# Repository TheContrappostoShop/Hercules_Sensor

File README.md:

# Hercules Force Sensor 

Hercules is the open-source force sensor made for the Prometheus mSLA, based on the idea of Nico Martin (Concepts3D).

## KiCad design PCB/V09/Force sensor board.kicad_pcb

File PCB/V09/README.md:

The version 0.9 of the Hercules sensor is the prerelease (beta) of it.

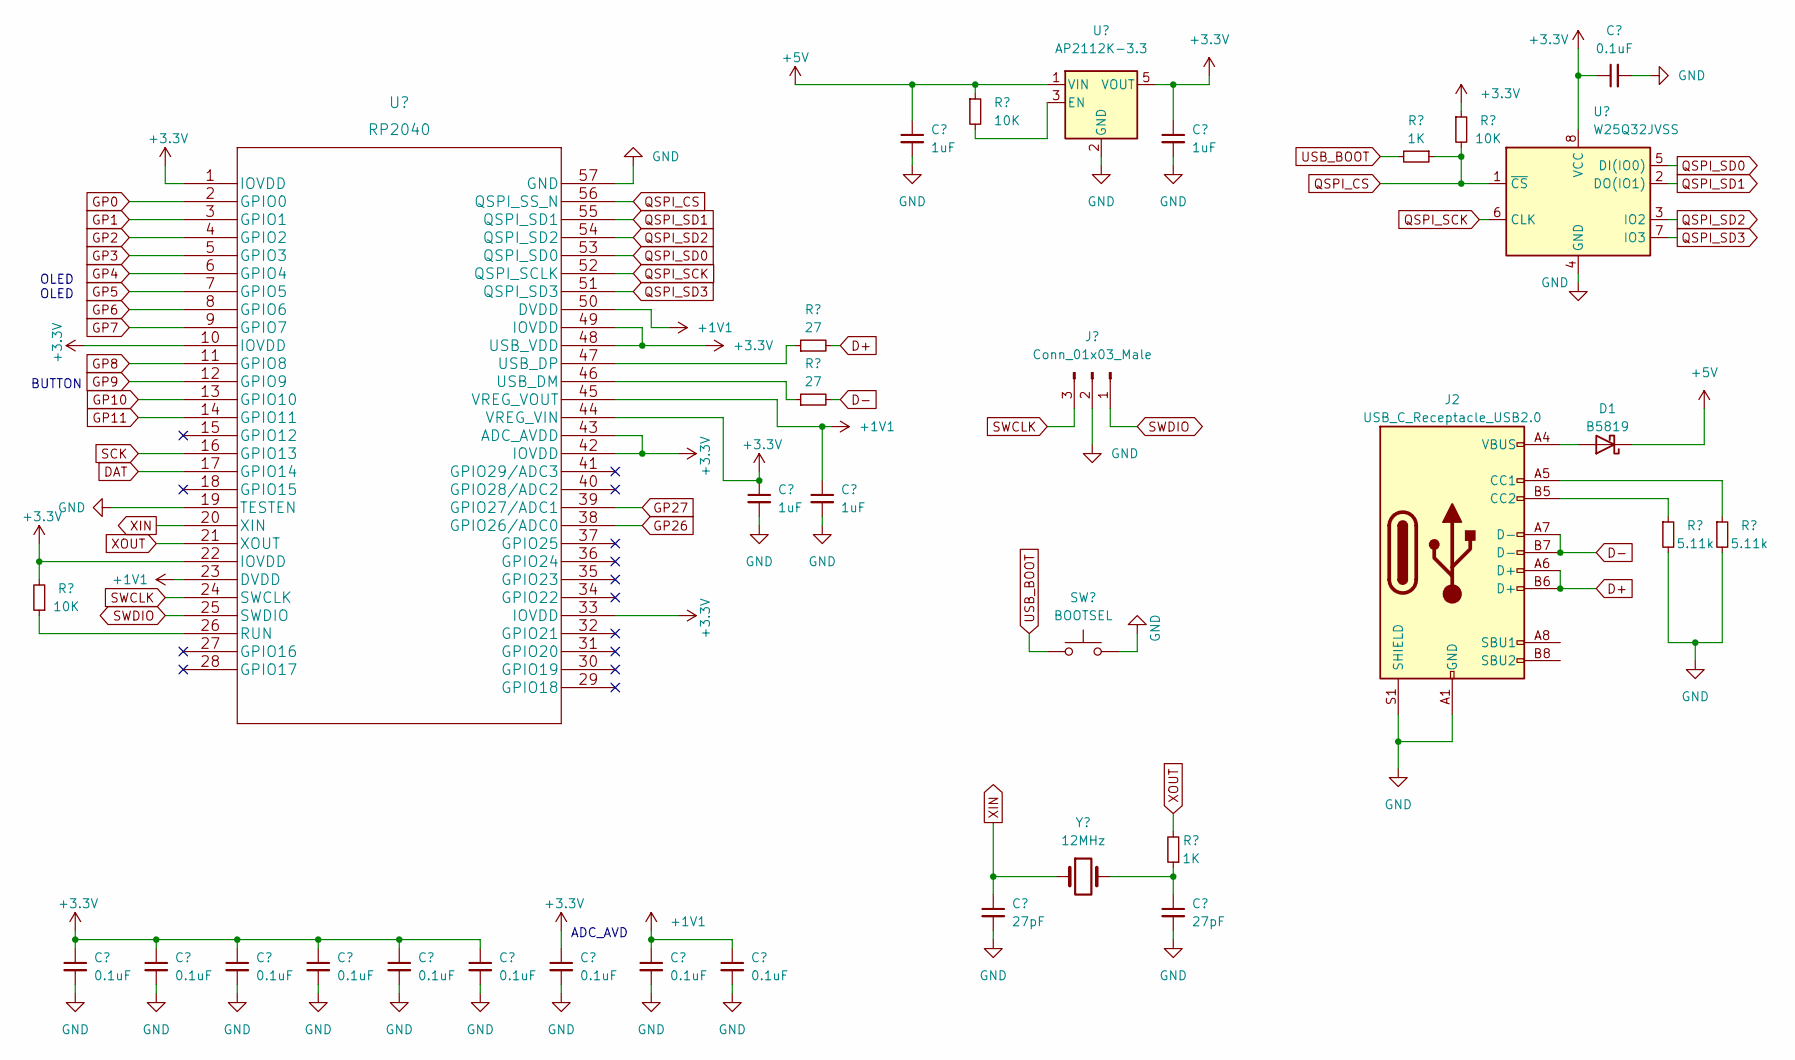
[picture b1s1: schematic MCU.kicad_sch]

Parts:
C1, C8, C9, C10, C11, C12, C13, C14, C15, C16: 0.1uF; C_0603_1608Metric
C2, C3, C4, C5: 1uF; C_0603_1608Metric
C6, C7: 27pF; C_0603_1608Metric
D1: B5819; D_SOD-123
J1: Conn_01x03_Male; PinHeader_1x03_P1.27mm_Vertical
J2: USB_C_Receptacle_USB2.0; USB_C_Receptacle_GCT_USB4115-03-C
R1, R2, R8: 10K; R_0603_1608Metric
R3, R9: 1K; R_0603_1608Metric
R4, R5: 27; R_0603_1608Metric
R6, R7: 5.11k; R_0603_1608Metric
SW1: BOOTSEL; SW_Push_SPST_NO_Alps_SKRK
U1: AP2112K-3.3; SOT-23-5
U2: RP2040; QFN-56-1EP_7x7mm_P0.4mm_EP3.2x3.2mm
U3: W25Q32JVSS; SOIC-8_5.23x5.23mm_P1.27mm
Y1: 12MHz; Crystal_SMD_3225-4Pin_3.2x2.5mm

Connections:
+1V1: C5.1, C15.1, C16.1, U2.23 (DVDD), U2.45 (VREG_VOUT), U2.50 (DVDD)
+3V3: C1.1, C3.1, C4.1, C8.1, C9.1, C10.1, C11.1, C12.1, C13.1, C14.1, R2.1, R8.2, U1.5 (VOUT), U2.1 (IOVDD), U2.10 (IOVDD), U2.22 (IOVDD), U2.33 (IOVDD), U2.42 (IOVDD), U2.43 (ADC_AVDD), U2.44 (VREG_VIN), U2.48 (USB_VDD), U2.49 (IOVDD), U3.8 (VCC); also elsewhere on the board
+5V: C2.1, D1.1 (K), R1.1, U1.1 (VIN); also elsewhere on the board
D+: J2.A6 (D+), J2.B6 (D+), R4.2
D-: J2.A7 (D-), J2.B7 (D-), R5.2
DAT: U2.17 (GPIO14); also elsewhere on the board
GP0: U2.2 (GPIO0); also elsewhere on the board
GP1: U2.3 (GPIO1); also elsewhere on the board
GP2: U2.4 (GPIO2); also elsewhere on the board
GP3: U2.5 (GPIO3); also elsewhere on the board
GP4: U2.6 (GPIO4); also elsewhere on the board
GP5: U2.7 (GPIO5); also elsewhere on the board
GP6: U2.8 (GPIO6); also elsewhere on the board
GP7: U2.9 (GPIO7); also elsewhere on the board
GP8: U2.11 (GPIO8); also elsewhere on the board
GP9: U2.12 (GPIO9); also elsewhere on the board
GP10: U2.13 (GPIO10)
GP11: U2.14 (GPIO11)
GP26: U2.38 (GPIO26/ADC0); also elsewhere on the board
GP27: U2.39 (GPIO27/ADC1); also elsewhere on the board
unnamed: D1.2 (A), J2.A4 (VBUS), J2.A9 (VBUS), J2.B4 (VBUS), J2.B9 (VBUS)
unnamed: J2.A5 (CC1), R7.1
unnamed: J2.B5 (CC2), R6.1
unnamed: R1.2, U1.3 (EN)
unnamed: R8.1, U2.26 (RUN)
unnamed: R5.1, U2.46 (USB_DM)
unnamed: R4.1, U2.47 (USB_DP)
unnamed: C7.1, R9.1, Y1.3 (2)
QSPI_CS: R2.2, R3.1, U2.56 (QSPI_SS_N), U3.1 (~CS)
QSPI_SCK: U2.52 (QSPI_SCLK), U3.6 (CLK)
QSPI_SD0: U2.53 (QSPI_SD0), U3.5 (DI(IO0))
QSPI_SD1: U2.55 (QSPI_SD1), U3.2 (DO(IO1))
QSPI_SD2: U2.54 (QSPI_SD2), U3.3 (IO2)
QSPI_SD3: U2.51 (QSPI_SD3), U3.7 (IO3)
SCK: U2.16 (GPIO13); also elsewhere on the board
SWCLK: J1.3, U2.24 (SWCLK)
SWDIO: J1.1, U2.25 (SWDIO)
XIN: C6.1, U2.20 (XIN), Y1.1
XOUT: R9.2, U2.21 (XOUT)

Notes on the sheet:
BUTTON
ADC_AVD
OLED OLED

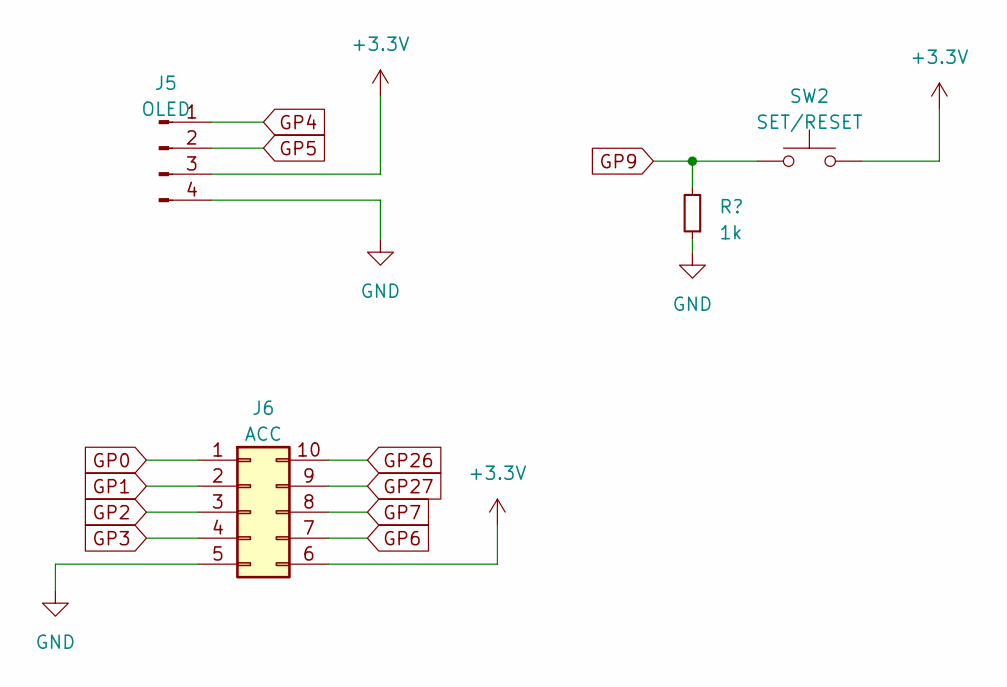
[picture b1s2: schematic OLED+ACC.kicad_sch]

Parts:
J5: OLED; PinHeader_1x04_P2.54mm_Vertical
J6: ACC; PinHeader_2x05_P1.27mm_Vertical
R17: 1k; R_0603_1608Metric
SW2: SET/RESET; SW_Push_SPST_NO_Alps_SKRK

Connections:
+3V3: J5.3, J6.6, SW2.2; also elsewhere on the board
GP0: J6.1; also elsewhere on the board
GP1: J6.2; also elsewhere on the board
GP2: J6.3; also elsewhere on the board
GP3: J6.4; also elsewhere on the board
GP4: J5.1; also elsewhere on the board
GP5: J5.2; also elsewhere on the board
GP6: J6.7; also elsewhere on the board
GP7: J6.8; also elsewhere on the board
GP9: R17.2, SW2.1; also elsewhere on the board
GP26: J6.10; also elsewhere on the board
GP27: J6.9; also elsewhere on the board

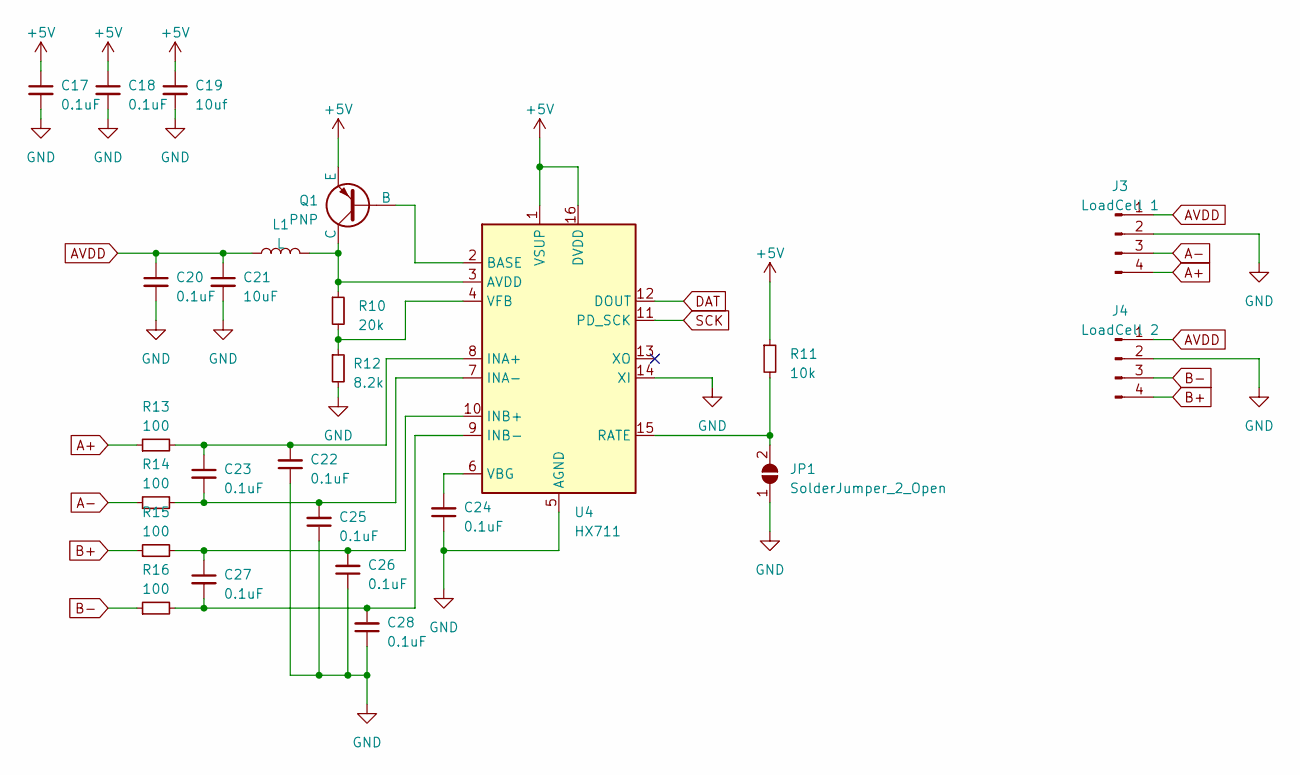
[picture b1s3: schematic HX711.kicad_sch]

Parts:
C17, C18, C20, C22, C23, C24, C25, C26, C27, C28: 0.1uF; C_0603_1608Metric
C19: 10uf; C_0603_1608Metric
C21: 10uF; C_0603_1608Metric
J3: LoadCell 1; Molex_KK-254_AE-6410-04A_1x04_P2.54mm_Vertical
J4: LoadCell 2; Molex_KK-254_AE-6410-04A_1x04_P2.54mm_Vertical
JP1: SolderJumper_2_Open; SolderJumper-2_P1.3mm_Open_RoundedPad1.0x1.5mm
L1: L; L_0603_1608Metric
Q1: PNP; SOT-23
R10: 20k; R_0603_1608Metric
R11: 10k; R_0603_1608Metric
R12: 8.2k; R_0603_1608Metric
R13, R14, R15, R16: 100; R_0603_1608Metric
U4: HX711; SOP-16_3.9x9.9mm_P1.27mm

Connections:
+5V: C17.1, C18.1, C19.1, Q1.3 (E), R11.1, U4.1 (VSUP), U4.16 (DVDD); also elsewhere on the board
A+: J3.4, R13.1
A-: J3.3, R14.1
AVDD: C20.1, C21.1, J3.1, J4.1, L1.1
B+: J4.4, R15.1
B-: J4.3, R16.1
DAT: U4.12 (DOUT); also elsewhere on the board
unnamed: JP1.2 (B), R11.2, U4.15 (RATE)
unnamed: Q1.2 (B), U4.2 (BASE)
unnamed: L1.2, Q1.1 (C), R10.1, U4.3 (AVDD)
unnamed: C22.2, C23.1, R13.2, U4.8 (INA+)
unnamed: C23.2, C25.2, R14.2, U4.7 (INA-)
unnamed: C26.2, C27.1, R15.2, U4.10 (INB+)
unnamed: C27.2, C28.2, R16.2, U4.9 (INB-)
unnamed: C24.2, U4.6 (VBG)
unnamed: R10.2, R12.1, U4.4 (VFB)
SCK: U4.11 (PD_SCK); also elsewhere on the board

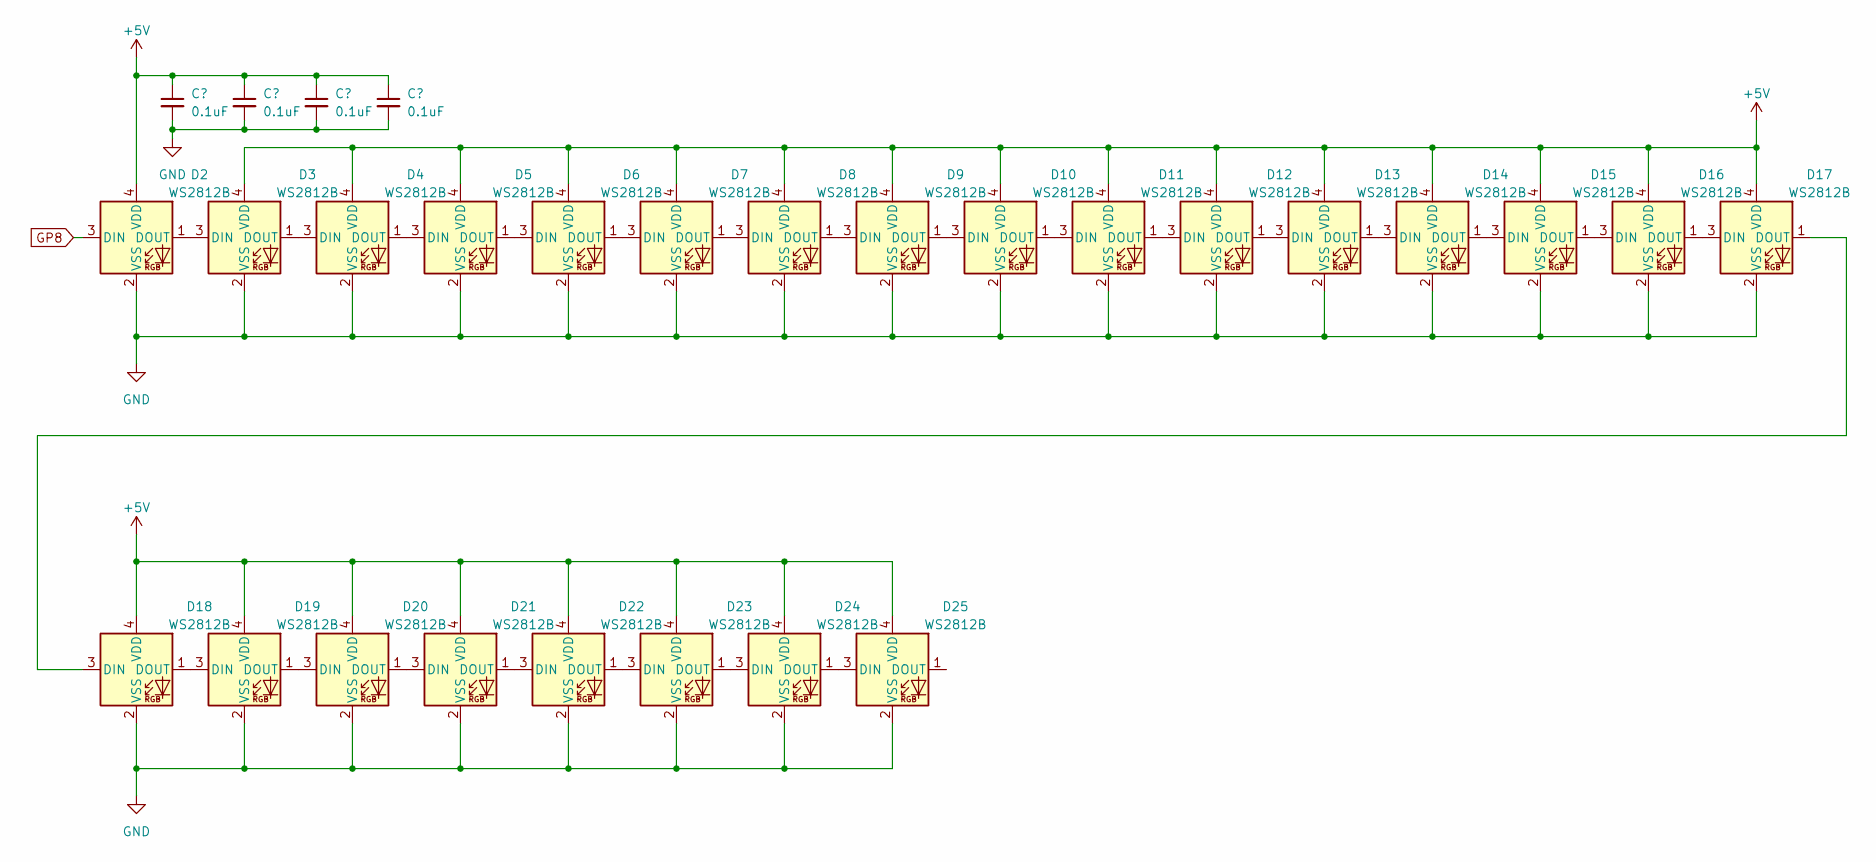
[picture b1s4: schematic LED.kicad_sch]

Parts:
C29, C30, C31, C32: 0.1uF; C_0603_1608Metric
D2, D3, D4, D5, D6, D7, D8, D9, D10, D11, D12, D13, D14, D15, D16, D17, D18, D19, D20, D21, D22, D23, D24, D25: WS2812B; LED_WS2812B-2020_PLCC4_2.0x2.0mm

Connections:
+5V: C29.1, C30.1, C31.1, C32.1, D2.4 (VDD), D3.4 (VDD), D4.4 (VDD), D5.4 (VDD), D6.4 (VDD), D7.4 (VDD), D8.4 (VDD), D9.4 (VDD), D10.4 (VDD), D11.4 (VDD), D12.4 (VDD), D13.4 (VDD), D14.4 (VDD), D15.4 (VDD), D16.4 (VDD), D17.4 (VDD), D18.4 (VDD), D19.4 (VDD), D20.4 (VDD), D21.4 (VDD), D22.4 (VDD), D23.4 (VDD), D24.4 (VDD), D25.4 (VDD); also elsewhere on the board
GP8: D2.3 (DIN); also elsewhere on the board
unnamed: D2.1 (DOUT), D3.3 (DIN)
unnamed: D3.1 (DOUT), D4.3 (DIN)
unnamed: D4.1 (DOUT), D5.3 (DIN)
unnamed: D5.1 (DOUT), D6.3 (DIN)
unnamed: D6.1 (DOUT), D7.3 (DIN)
unnamed: D7.1 (DOUT), D8.3 (DIN)
unnamed: D8.1 (DOUT), D9.3 (DIN)
unnamed: D9.1 (DOUT), D10.3 (DIN)
unnamed: D10.1 (DOUT), D11.3 (DIN)
unnamed: D11.1 (DOUT), D12.3 (DIN)
unnamed: D12.1 (DOUT), D13.3 (DIN)
unnamed: D13.1 (DOUT), D14.3 (DIN)
unnamed: D14.1 (DOUT), D15.3 (DIN)
unnamed: D15.1 (DOUT), D16.3 (DIN)
unnamed: D16.1 (DOUT), D17.3 (DIN)
unnamed: D17.1 (DOUT), D18.3 (DIN)
unnamed: D18.1 (DOUT), D19.3 (DIN)
unnamed: D19.1 (DOUT), D20.3 (DIN)
unnamed: D20.1 (DOUT), D21.3 (DIN)
unnamed: D21.1 (DOUT), D22.3 (DIN)
unnamed: D22.1 (DOUT), D23.3 (DIN)
unnamed: D23.1 (DOUT), D24.3 (DIN)
unnamed: D24.1 (DOUT), D25.3 (DIN)

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
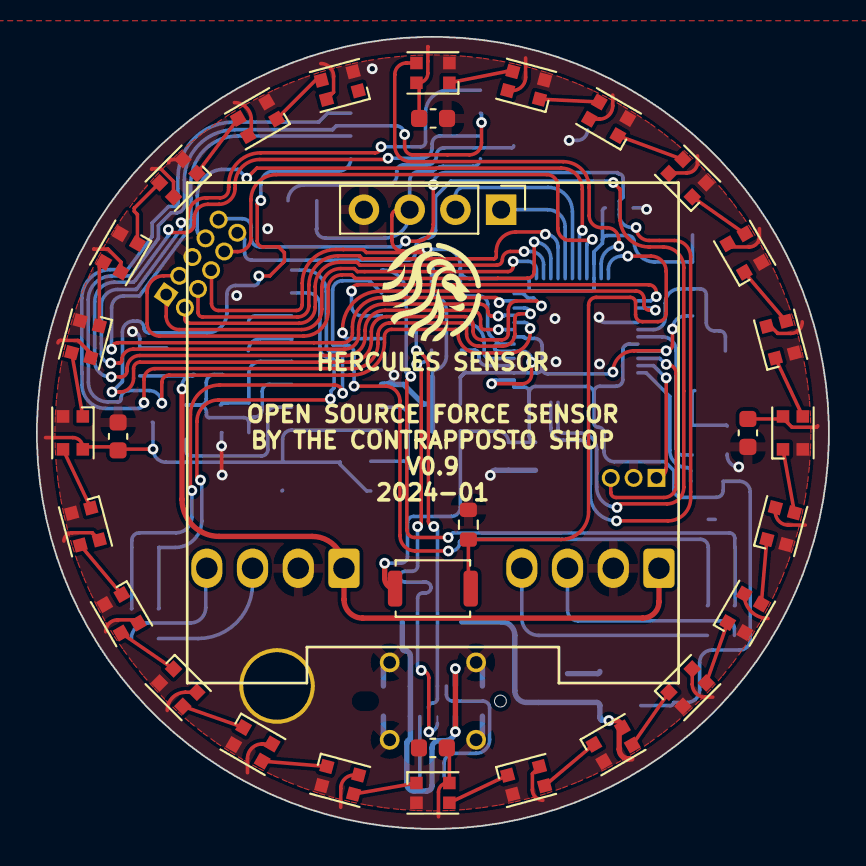
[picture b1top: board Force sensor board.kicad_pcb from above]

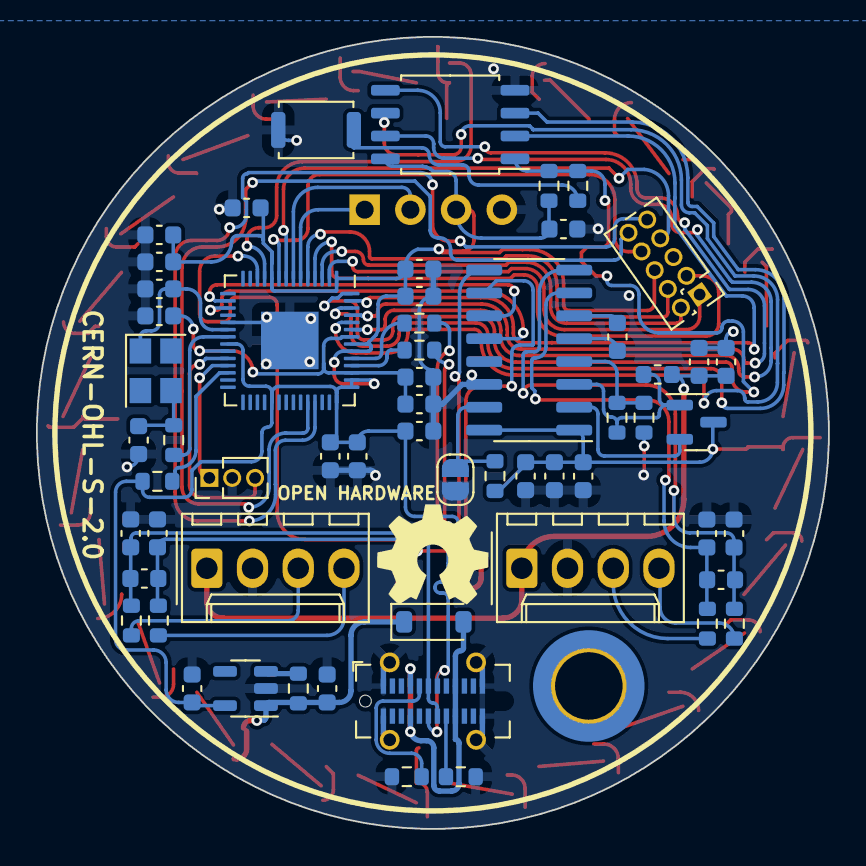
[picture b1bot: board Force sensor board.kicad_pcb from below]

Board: 2 copper layers, 44.0 x 44.0 mm, 90 parts (59 on the bottom side), 76 nets.

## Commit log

2024-01-22 Create PCB
2024-01-22 adding the kicad project files
2024-01-22 Add exemple code
2024-01-22 Delete PCB/Code directory
    wrong path
2024-02-16 Upload images
2024-02-16 Rename PCB buttom.png to PCBbuttom.png
2024-02-16 Rename PCB top.png to PCBtop.png
2024-02-16 Create LICENSE
2024-03-10 Update ForceSensor.ino code
2024-05-31 Update code
    more advance LED status, calibration and settings
2024-06-09 Update code

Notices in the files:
PCB/V09/Force sensor board.kicad_pcb:
CERN-OHL-S-2.0
